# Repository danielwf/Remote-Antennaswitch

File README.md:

# ESP32 Antenna Switch 

for the Remote Club Station of [DARC Bremen (i04)](https://darc.de/i04)\
\
**This is a draft!** \
There is no guarantee of functionality. Use at your own risk. 

## Description

The antenna switch can be controlled via the ESP32 either by USB or WiFi. Two buttons can be connected for local control. The switched inputs and outputs are also indicated by LEDs.  
The 3 inputs and 5 outputs are switched using two bistable relays per connection (Finder 40.31.6.006.0000). These are controlled by drivers that can be put into sleep mode between switching operations (DRV8833PWP). This reduces power consumption and minimizes interference from busy switching regulators. In addition, the USB port of the ESP32 is sufficient for the power supply.  
The relay drivers are controlled via an I2C 16-bit port expander (MCP23017).  
In addition, a PWR/SWR meter is available via an I2C AD converter (ADS1115IDGS). This is used to prevent switching during transmission. It can also be used for transmitter-independent measurement to display transmission power and SWR in the remote software.  

Since both the relay switching and the reading of the SWR bridge are communicated via I2C, other controllers can also be used if necessary. It is also possible to connect several boards together. For this purpose, the I2C addresses can be easily adjusted via the solder pads.  

## Built

**Kicad 9:**
You maybe need the KiCad symbol and footprint for the ESP32 Mini(Wemos D1 Mini) [https://github.com/r0oland/ESP32_mini_KiCad_Library](https://github.com/r0oland/ESP32_mini_KiCad_Library) - Thanks to [Johannes Rebling](https://github.com/r0oland)

[Schematic](schematic.pdf)

**Hardware:**
Everything you need to prepare your PCB ordering with KiCAD is included. It is best to use a corresponding KiCAD plugin for this.  
In "BOM.ods" you will find the material list with links to the item numbers at Mouser and Reichelt. In the table, you can easily adjust how many devices the parts should be ordered for (as of Oct-25).  
The BOM includes a housing that is well suited for this purpose. The drill holes for the circuit board can be easily marked with an unassembled PCB (which should be done first). "Panels.svg" contains the drill holes and labels for the buttons, LEDs, and connection sockets. These can be produced using a vinyl cutter or laser engraver, for example. The easiest way to create the USB socket is to drill a 14 mm hole and produce a cover for it using a 3D printer. A template for this is also included.  
Once the parts have been assembled, the Arduino code for the ESP32 can be uploaded. You will find this in “AntennaSwitch-ESP32.ino”. For later OTA updates via the web interface, you can use “AntennaSwitch-ESP32.ino.bin”.  

## Usage WIFI
</img> After you have uploaded the Arduino code to the ESP32, you must connect to the “AntSwitch-Config” Wi-Fi network and set up the desired Wi-Fi network via the captive portal. 
Once the device is connected to your home network, you can configure it via 'https://antswitch.local' such as a new host name and the labels for the connectors. **Default password for 'admin' is 'antswitch'**.  
You can also switch via API (example: you want to use CURL in your shell/script, maybe in combination with rigctld). Examples: 
- http://antswitch.local/api/status (for JSON-Status)
- http://antswitch.local/api/switch?input=1 (set input to 1)
- http://antswitch.local/api/switch?output=2 (set output to 2)
Setup via API:
- http://antswitch.local/api/switch?iLabel1=IC-7300 (set Label of input 1)
- http://antswitch.local/api/switch?oLabel2=Windom-Antenna (set Label of output 2)
- http://antswitch.local/api/switch?defaultInput=1 (set default input after switch-on)
- http://antswitch.local/api/switch?defaultOutput=2 (set default output after switch-on)
- http://antswitch.local/api/status?maxTxPower=380 (Calibration of SWR-Meter acc to windings on transformer- or just try out and compare to other SWR-Meter)

## Usage USB-serial
The device can also be controlled via the USB-serial interface (115200 baud). With “GET:NET” you can display the current IP address.  
Serial commands: 
```
       ____DESCRIPTION__________INPUT_________________________RESPONSE___________________________________  
       Switching  
       Switch Input (TRX)          SET:I<Index>                  ACK:I<CurrentInput>,O<CurrentOutput>  
                                                                ERR:BLOCKED_TX (if P_fwd > 5.0W)  
       Switch Output (Antenna)     SET:O<Index>                  ACK:I<CurrentInput>,O<CurrentOutput>  
                                                                ERR:BLOCKED_TX (if P_fwd > 5.0W)  
       ___________________________________________________________________________________________________
       Configuration
       Set Input Label             SET_LABEL I <Index> <Label>   ACK:LABEL_OK
                                                                ERR:INVALID_LENGTH
       Set Output Label            SET_LABEL O <Index> <Label>   ACK:LABEL_OK
                                                                ERR:INVALID_LENGTH
       Set Default Input           SET_DEFAULT I <Index>         ACK:DEFAULT_OK
                                                                ERR:INVALID_INDEX
       Set Default Output          SET_DEFAULT O <Index>         ACK:DEFAULT_OK
                                                                ERR:INVALID_INDEX
       Set Admin Password          SET_PASS <Password>           ACK:PASS_OK
                                                                ERR:INVALID_LENGTH (min 8 chars)
       ___________________________________________________________________________________________________
       Status and Measurements
       Get All Status & Meas.      GET:STATUS                    ACK:STATUS,PF=x.x,PP=x.x,SWR=x.xx
       Get Forward Power (Formatted) GET:PF                        ACK:PF=x.x
       Get Peak Power (Formatted)  GET:PP                        ACK:PP=x.x
       Get SWR Value (Formatted)   GET:SWR                       ACK:SWR=x.xx
       Get Forward Power (Numeric) NUM:PF                        [x.x] (Unformatted numeric value)
       Get Peak Power (Numeric)    NUM:PP                        [x.x] (Unformatted numeric value)
       Get SWR Value (Numeric)     NUM:SWR                       [x.xx] (Unformatted numeric value)
       Get IP and Hostname         GET:NET                       ACK:NET,IP=x.x.x.x,HOST=<Hostname>
       Get Input Label             GET_LABEL I <Index>           ACK:LABEL_I<Index>=<Label>
       Get Output Label            GET_LABEL O <Index>           ACK:LABEL_O<Index>=<Label>
```

## Contributing

Pull requests are welcome. For major changes, please open an issue first
to discuss what you would like to change.

## License

[CC BY-SA 4.0](https://creativecommons.org/licenses/by-sa/4.0/)

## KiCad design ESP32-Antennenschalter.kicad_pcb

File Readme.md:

# ESP32 Antenna Switch 

for the Remote Club Station of [DARC Bremen (i04)](https://darc.de/i04)\
\
**This is a draft!** \
There is no guarantee of functionality. Use at your own risk. 

**ToDos**
 - BOM
 - 3D design for FDM printers and shielding
 - Arduino Code
 - first builds

## Description

The antenna switch can be controlled via the ESP32 either by USB, WiFi, or Bluetooth, depending on what is implemented in the code. Two buttons can be connected for local control. The switched inputs and outputs are also indicated by LEDs. 

The 3 inputs and 5 outputs are switched using two bistable relays per connection (Finder 40.31.6.006.0000). These are controlled by drivers that can be put into sleep mode between switching operations (DRV8833PWP). This reduces power consumption and minimizes interference from busy switching regulators. In addition, the USB port of the ESP32 is sufficient for the power supply. 

The relay drivers are controlled via an I2C 16-bit port expander (MCP23017). 
In addition, a PWR/SWR meter is available via an I2C AD converter (ADS1115IDGS). This is used to prevent switching during transmission. It can also be used for transmitter-independent measurement to display transmission power and SWR in the remote software. 

Since both the relay switching and the reading of the SWR bridge are communicated via I2C, other controllers can also be used if necessary. It is also possible to connect several boards together. For this purpose, the I2C addresses can be easily adjusted via the solder pads. 

## Usage

**Kicad 9:**
You maybe need the KiCad symbol and footprint for the ESP32 Mini(Wemos D1 Mini) [https://github.com/r0oland/ESP32_mini_KiCad_Library](https://github.com/r0oland/ESP32_mini_KiCad_Library) - Thanks to [Johannes Rebling](https://github.com/r0oland)

## Contributing

Pull requests are welcome. For major changes, please open an issue first
to discuss what you would like to change.

## License

[CC BY-SA 4.0](https://creativecommons.org/licenses/by-sa/4.0/)

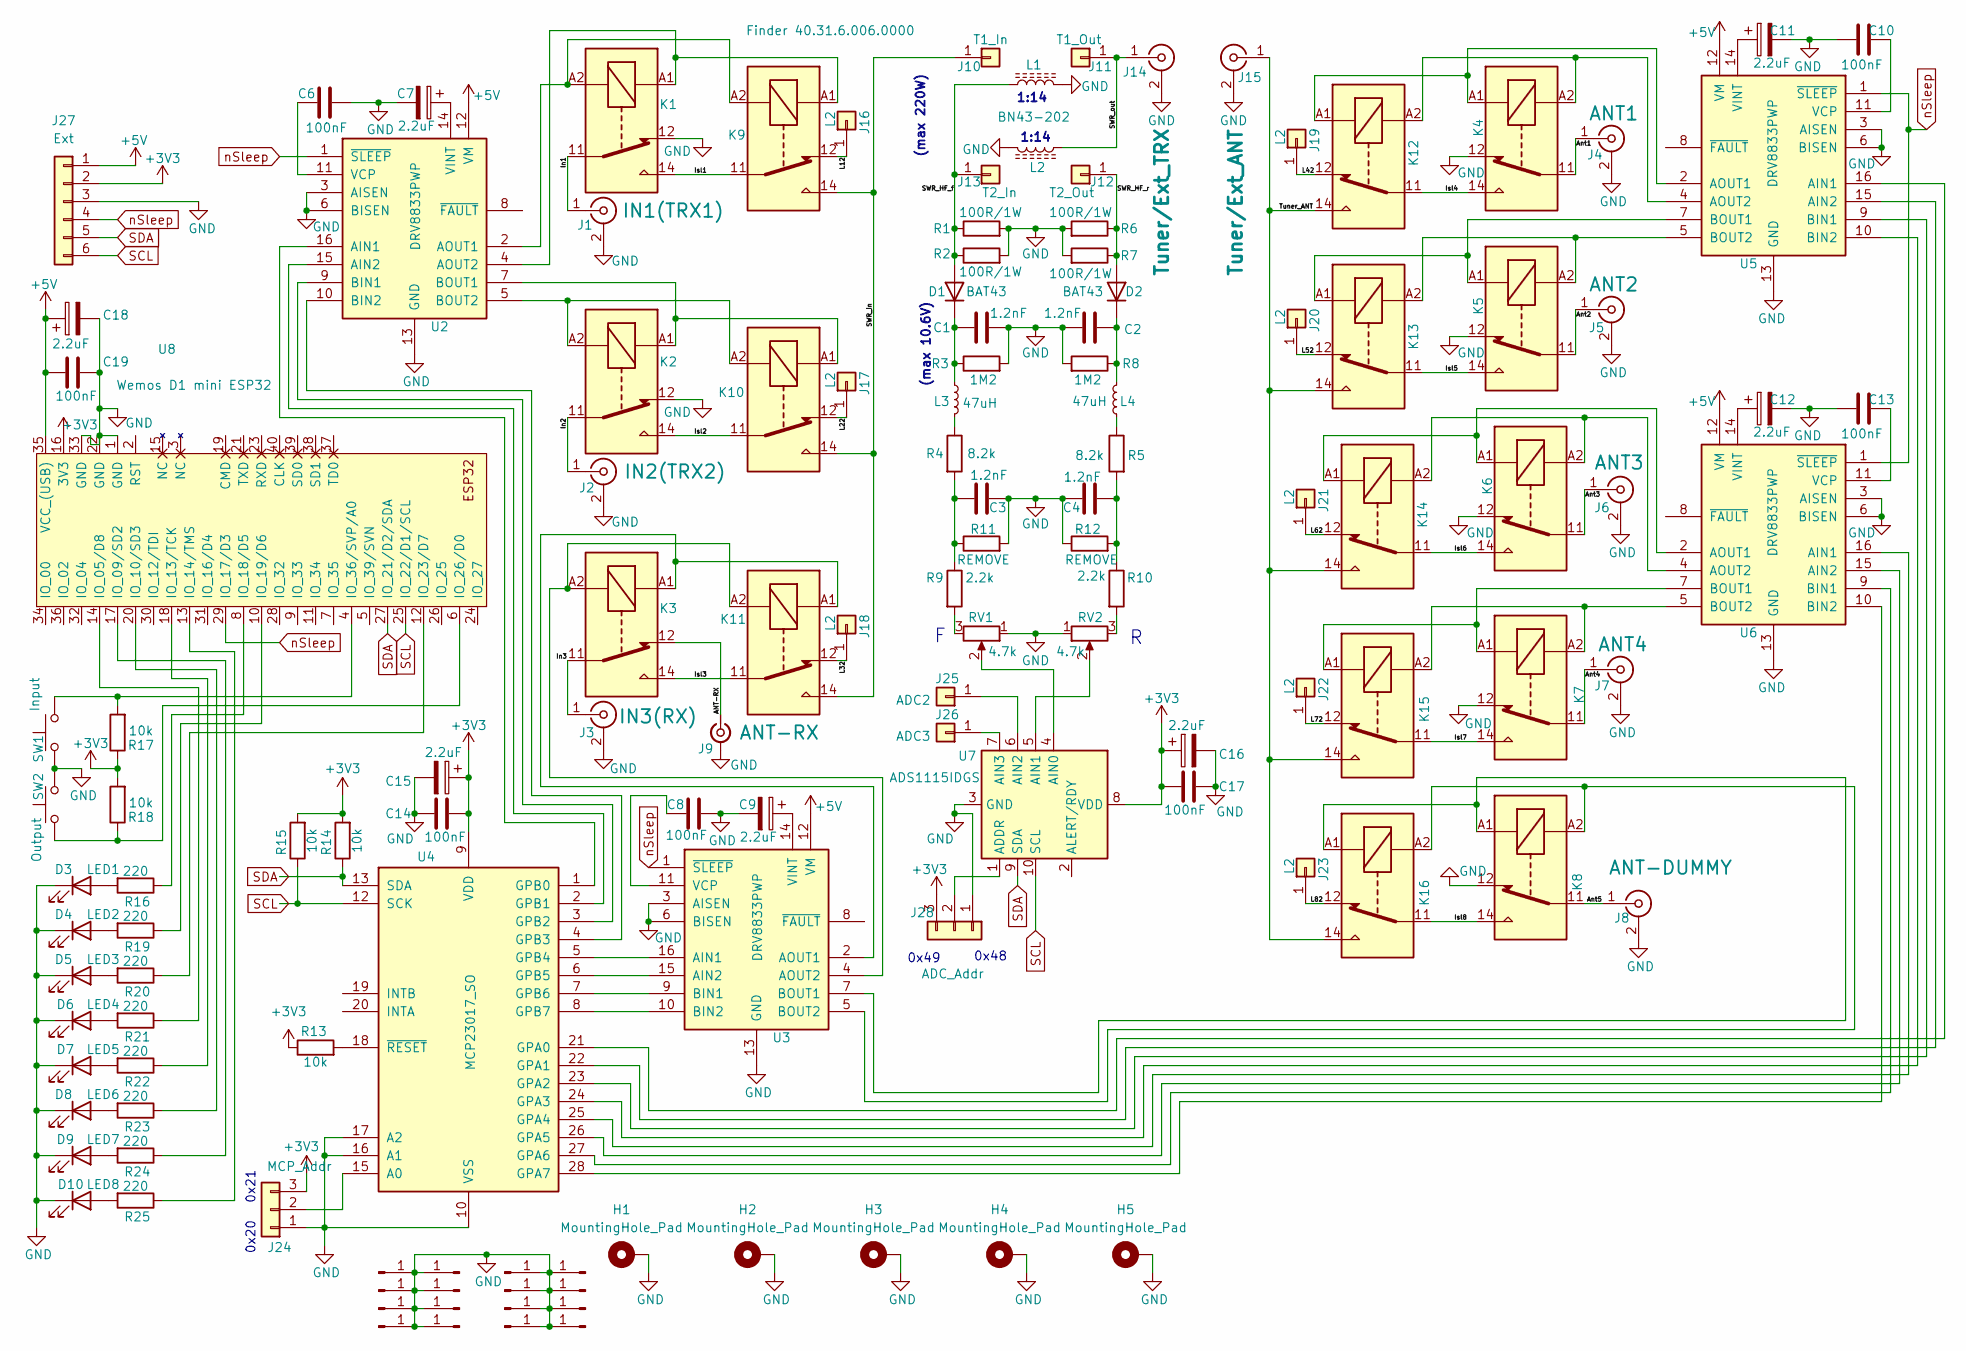
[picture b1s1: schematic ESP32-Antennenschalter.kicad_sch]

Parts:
C1, C2, C3, C4: 1.2nF; C_Disc_D4.3mm_W1.9mm_P5.00mm
C6, C8, C10, C13, C14, C17, C19: 100nF; C_Disc_D4.3mm_W1.9mm_P5.00mm
C7, C9, C11, C12, C15, C16, C18: 2.2uF; CP_Radial_D5.0mm_P2.00mm
D1, D2: BAT43; D_DO-35_SOD27_P7.62mm_Horizontal
D3: LED1; LED_D3.0mm
D4: LED2; LED_D3.0mm
D5: LED3; LED_D3.0mm
D6: LED4; LED_D3.0mm
D7: LED5; LED_D3.0mm
D8: LED6; LED_D3.0mm
D9: LED7; LED_D3.0mm
D10: LED8; LED_D3.0mm
H1, H2, H3, H4, H5: MountingHole_Pad; MountingHole_3.2mm_M3_DIN965_Pad_TopBottom
J1: IN1(TRX1); TerminalBlock_bornier-2_P5.08mm
J2: IN2(TRX2); TerminalBlock_bornier-2_P5.08mm
J3: IN3(RX); TerminalBlock_bornier-2_P5.08mm
J4: ANT1; TerminalBlock_bornier-2_P5.08mm
J5: ANT2; TerminalBlock_bornier-2_P5.08mm
J6: ANT3; TerminalBlock_bornier-2_P5.08mm
J7: ANT4; TerminalBlock_bornier-2_P5.08mm
J8: ANT-DUMMY; TerminalBlock_bornier-2_P5.08mm
J9: ANT-RX; PinHeader_1x02_P2.54mm_Vertical
J10: T1_In; Pin_D1.3mm_L11.0mm_LooseFit
J11: T1_Out; Pin_D1.3mm_L11.0mm_LooseFit
J12: T2_Out; Pin_D1.3mm_L11.0mm_LooseFit
J13: T2_In; Pin_D1.3mm_L11.0mm_LooseFit
J14: Tuner/Ext_TRX; TerminalBlock_bornier-2_P5.08mm
J15: Tuner/Ext_ANT; TerminalBlock_bornier-2_P5.08mm
J16, J17, J18, J19, J20, J21, J22, J23: L2; Pin_D0.7mm_L6.5mm_W1.8mm_FlatFork
J24: MCP_Addr; SolderJumper-3_P1.3mm_Bridged2Bar12_Pad1.0x1.5mm_NumberLabe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
J25: ADC2; Pin_D0.7mm_L6.5mm_W1.8mm_FlatFork
J26: ADC3; Pin_D0.7mm_L6.5mm_W1.8mm_FlatFork
J27: Ext; PinHeader_1x06_P2.54mm_Vertical
J28: ADC_Addr; SolderJumper-3_P1.3mm_Bridged2Bar12_Pad1.0x1.5mm_NumberLabe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
J29, J30, J31, J32, J33, J34, J35, J36, J37, J38, J39, J40, J41, J42, J43, J44: Conn_01x01_Pin; Pin_D0.7mm_L6.5mm_W1.8mm_FlatFork
K1, K2, K3, K4, K5, K6, K7, K8, K9, K10, K11, K12, K13, K14, K15, K16: Finder 40.31.6.006.0000; Relay_SPDT_Finder_40.31
L1, L2: BN43-202; L_Axial_L14.5mm_D5.8mm_P25.40mm_Horizontal_Fastron_HBCC
L3, L4: 47uH; L_Axial_L7.0mm_D3.3mm_P10.16mm_Horizontal_Fastron_MICC
R1, R2, R6, R7: 100R/1W; R_Axial_DIN0207_L6.3mm_D2.5mm_P5.08mm_Vertical
R3, R8: 1M2; R_Axial_DIN0207_L6.3mm_D2.5mm_P5.08mm_Vertical
R4, R5: 8.2k; R_Axial_DIN0207_L6.3mm_D2.5mm_P5.08mm_Vertical
R9, R10: 2.2k; R_Axial_DIN0207_L6.3mm_D2.5mm_P5.08mm_Vertical
R11, R12: REMOVE; R_Axial_DIN0207_L6.3mm_D2.5mm_P5.08mm_Vertical
R13, R14, R15, R17, R18: 10k; R_Axial_DIN0204_L3.6mm_D1.6mm_P7.62mm_Horizontal
R16, R19, R20, R21, R22, R23, R24, R25: 220; R_Axial_DIN0204_L3.6mm_D1.6mm_P7.62mm_Horizontal
RV1, RV2: 4.7k; Potentiometer_Vishay_T93YA_Vertical
SW1: Input; PinHeader_1x02_P2.54mm_Vertical
SW2: Output; PinHeader_1x02_P2.54mm_Vertical
U2, U3, U5, U6: DRV8833PWP; HTSSOP-16-1EP_4.4x5mm_P0.65mm_EP3.4x5mm_Mask2.46x2.31mm_The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
U4: MCP23017_SO; SOIC-28W_7.5x17.9mm_P1.27mm
U7: ADS1115IDGS; TSSOP-10_3x3mm_P0.5mm
U8: Wemos D1 mini ESP32; ESP32_mini

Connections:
+3V3: C14.1, C15.1, C16.1, C17.1, J24.3, J27.2, J28.3, R13.1, R14.2, R15.2, R17.1, R18.2, U4.9 (VDD), U7.8 (VDD), U8.16 (3V3)
+5V: C18.1, C19.2, J27.1, U2.12 (VM), U3.12 (VM), U5.12 (VM), U6.12 (VM), U8.35 (VCC_(USB))
/ANT-RX: J9.1 (In), K3.12
/Ant1: J4.1 (In), K4.11
/Ant2: J5.1 (In), K5.11
/Ant3: J6.1 (In), K6.11
/Ant4: J7.1 (In), K7.11
/Ant5: J8.1 (In), K8.11
/In1: J1.1 (In), K1.11
/In2: J2.1 (In), K2.11
/In3: J3.1 (In), K3.11
/Isl1: K1.14, K9.11
/Isl2: K2.14, K10.11
/Isl3: K3.14, K11.11
/Isl4: K4.14, K12.11
/Isl5: K5.14, K13.11
/Isl6: K6.14, K14.11
/Isl7: K7.14, K15.11
/Isl8: K8.14, K16.11
/L12: J16.1, K9.12
/L22: J17.1, K10.12
/L32: J18.1, K11.12
/L42: J19.1, K12.12
/L52: J20.1, K13.12
/L62: J21.1, K14.12
/L72: J22.1, K15.12
/L82: J23.1, K16.12
/SWR_HF_f: D1.2 (A), J13.1, L1.1, R1.1, R2.1
/SWR_HF_r: D2.2 (A), J12.1, R6.1, R7.1
/SWR_in: J10.1, K9.14, K10.14, K11.14
/SWR_out: J11.1, J14.1 (In), L2.1
/Tuner_ANT: J15.1 (In), K12.14, K13.14, K14.14, K15.14, K16.14
GND: C1.2, C2.2, C3.2, C4.1, C6.1, C7.2, C8.1, C9.2, C10.1, C11.2, C12.2, C13.1, C14.2, C15.2, C16.2, C17.2, C18.2, C19.1, D3.1 (K), D4.1 (K), D5.1 (K), D6.1 (K), D7.1 (K), D8.1 (K), D9.1 (K), D10.1 (K), H1.1, H2.1, H3.1, H4.1, H5.1, J1.2 (Ext), J2.2 (Ext), J3.2 (Ext), J4.2 (Ext), J5.2 (Ext), J6.2 (Ext), J7.2 (Ext), J8.2 (Ext), J9.2 (Ext), J14.2 (Ext), J15.2 (Ext), J24.1, J27.3, J28.1, J29.1, J30.1, J31.1, J32.1, J33.1, J34.1, J35.1, J36.1, J37.1, J38.1, J39.1, J40.1, J41.1, J42.1, J43.1, J44.1, K1.12, K2.12, K4.12, K5.12, K6.12, K7.12, K8.12, L1.2, L2.2, R1.2, R2.2, R3.2, R6.2, R7.2, R8.2, R11.2, R12.1, RV1.1, RV2.1, SW1.1, SW2.2, U2.3 (AISEN), U2.6 (BISEN), U2.13 (GND), U2.17 (GND), U3.3 (AISEN), U3.6 (BISEN), U3.13 (GND), U3.17 (GND), U4.10 (VSS), U4.16 (A1), U4.17 (A2), U5.3 (AISEN), U5.6 (BISEN), U5.13 (GND), U5.17 (GND), U6.3 (AISEN), U6.6 (BISEN), U6.13 (GND), U6.17 (GND), U7.3 (GND), U8.1 (GND), U8.22 (GND), U8.33 (GND)
unnamed: C3.1, R4.2, R9.1, R11.1
unnamed: C4.2, R5.2, R10.1, R12.2
unnamed: C1.1, D1.1 (K), L3.1, R3.1
unnamed: C2.1, D2.1 (K), L4.1, R8.1
unnamed: D3.2 (A), R16.2
unnamed: D4.2 (A), R19.2
unnamed: D5.2 (A), R20.2
unnamed: D6.2 (A), R21.2
unnamed: D7.2 (A), R22.2
unnamed: D8.2 (A), R23.2
unnamed: D9.2 (A), R24.2
unnamed: D10.2 (A), R25.2
unnamed: J24.2, U4.15 (A0)
unnamed: J25.1, U7.6 (AIN2)
unnamed: J26.1, U7.7 (AIN3)
unnamed: J28.2, U7.1 (ADDR)
unnamed: L3.2, R4.1
unnamed: L4.2, R5.1
unnamed: R9.2, RV1.3
unnamed: R10.2, RV2.3
unnamed: U2.16 (AIN1), U4.1 (GPB0)
unnamed: U2.15 (AIN2), U4.2 (GPB1)
unnamed: K1.A2, K9.A2, U2.2 (AOUT1)
unnamed: K1.A1, K9.A1, U2.4 (AOUT2)
unnamed: U2.9 (BIN1), U4.3 (GPB2)
unnamed: U2.10 (BIN2), U4.4 (GPB3)
unnamed: K2.A1, K10.A1, U2.7 (BOUT1)
unnamed: K2.A2, K10.A2, U2.5 (BOUT2)
unnamed: C6.2, U2.11 (VCP)
unnamed: C7.1, U2.14 (VINT)
unnamed: U3.16 (AIN1), U4.5 (GPB4)
unnamed: U3.15 (AIN2), U4.6 (GPB5)
unnamed: K3.A1, K11.A1, U3.2 (AOUT1)
unnamed: K3.A2, K11.A2, U3.4 (AOUT2)
unnamed: U3.9 (BIN1), U4.7 (GPB6)
unnamed: U3.10 (BIN2), U4.8 (GPB7)
unnamed: K8.A1, K16.A1, U3.7 (BOUT1)
unnamed: K8.A2, K16.A2, U3.5 (BOUT2)
unnamed: C8.2, U3.11 (VCP)
unnamed: C9.1, U3.14 (VINT)
unnamed: U4.21 (GPA0), U5.16 (AIN1)
unnamed: U4.22 (GPA1), U5.15 (AIN2)
unnamed: U4.23 (GPA2), U5.9 (BIN1)
unnamed: U4.24 (GPA3), U5.10 (BIN2)
unnamed: U4.25 (GPA4), U6.16 (AIN1)
unnamed: U4.26 (GPA5), U6.15 (AIN2)
unnamed: U4.27 (GPA6), U6.9 (BIN1)
unnamed: U4.28 (GPA7), U6.10 (BIN2)
unnamed: R13.2, U4.18 (~RESET)
unnamed: K4.A1, K12.A1, U5.2 (AOUT1)
unnamed: K4.A2, K12.A2, U5.4 (AOUT2)
unnamed: K5.A1, K13.A1, U5.7 (BOUT1)
unnamed: K5.A2, K13.A2, U5.5 (BOUT2)
unnamed: C10.2, U5.11 (VCP)
unnamed: C11.1, U5.14 (VINT)
unnamed: K6.A1, K14.A1, U6.2 (AOUT1)
unnamed: K6.A2, K14.A2, U6.4 (AOUT2)
unnamed: K7.A1, K15.A1, U6.7 (BOUT1)
unnamed: K7.A2, K15.A2, U6.5 (BOUT2)
unnamed: C13.2, U6.11 (VCP)
unnamed: C12.1, U6.14 (VINT)
unnamed: RV1.2, U7.4 (AIN0)
unnamed: RV2.2, U7.5 (AIN1)
unnamed: R21.1, U8.14 (IO_05/D8)
unnamed: R24.1, U8.17 (IO_09/SD2)
unnamed: R23.1, U8.20 (IO_10/SD3)
unnamed: R22.1, U8.18 (IO_13/TCK)
unnamed: R25.1, U8.13 (IO_14/TMS)
unnamed: R16.1, U8.8 (IO_18/D5)
unnamed: R19.1, U8.10 (IO_19/D6)
unnamed: R20.1, U8.12 (IO_23/D7)
unnamed: R18.1, SW2.1, U8.6 (IO_26/D0)
unnamed: R17.2, SW1.2, U8.4 (IO_36/SVP/A0)
SCL: J27.6, R15.1, U4.12 (SCK), U7.10 (SCL), U8.25 (IO_22/D1/SCL)
SDA: J27.5, R14.1, U4.13 (SDA), U7.9 (SDA), U8.27 (IO_21/D2/SDA)
nSleep: J27.4, U2.1 (~SLEEP), U3.1 (~SLEEP), U5.1 (~SLEEP), U6.1 (~SLEEP), U8.29 (IO_17/D3)

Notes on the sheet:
(max 10.6V)
0x20
0x49
0x48
(max 220W)
1:14
0x21

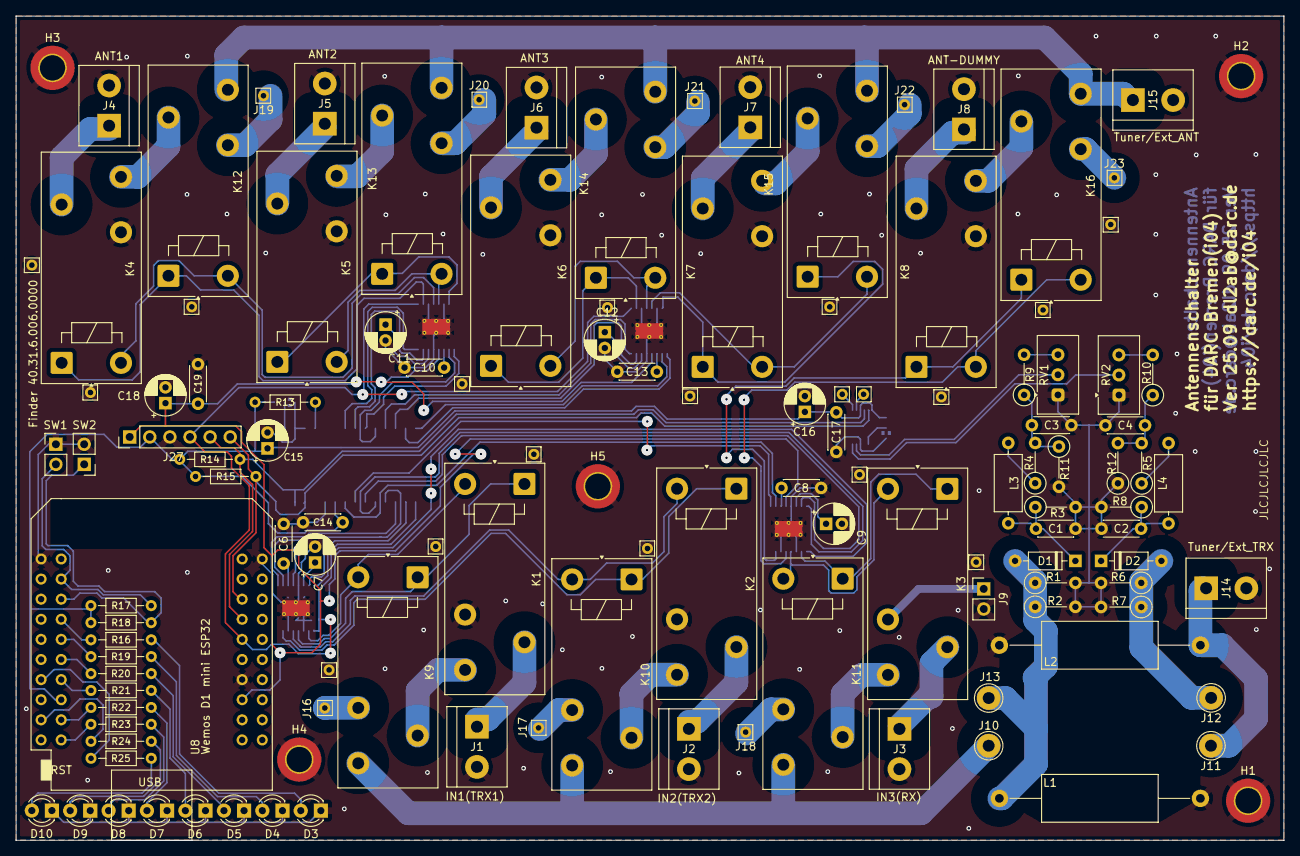
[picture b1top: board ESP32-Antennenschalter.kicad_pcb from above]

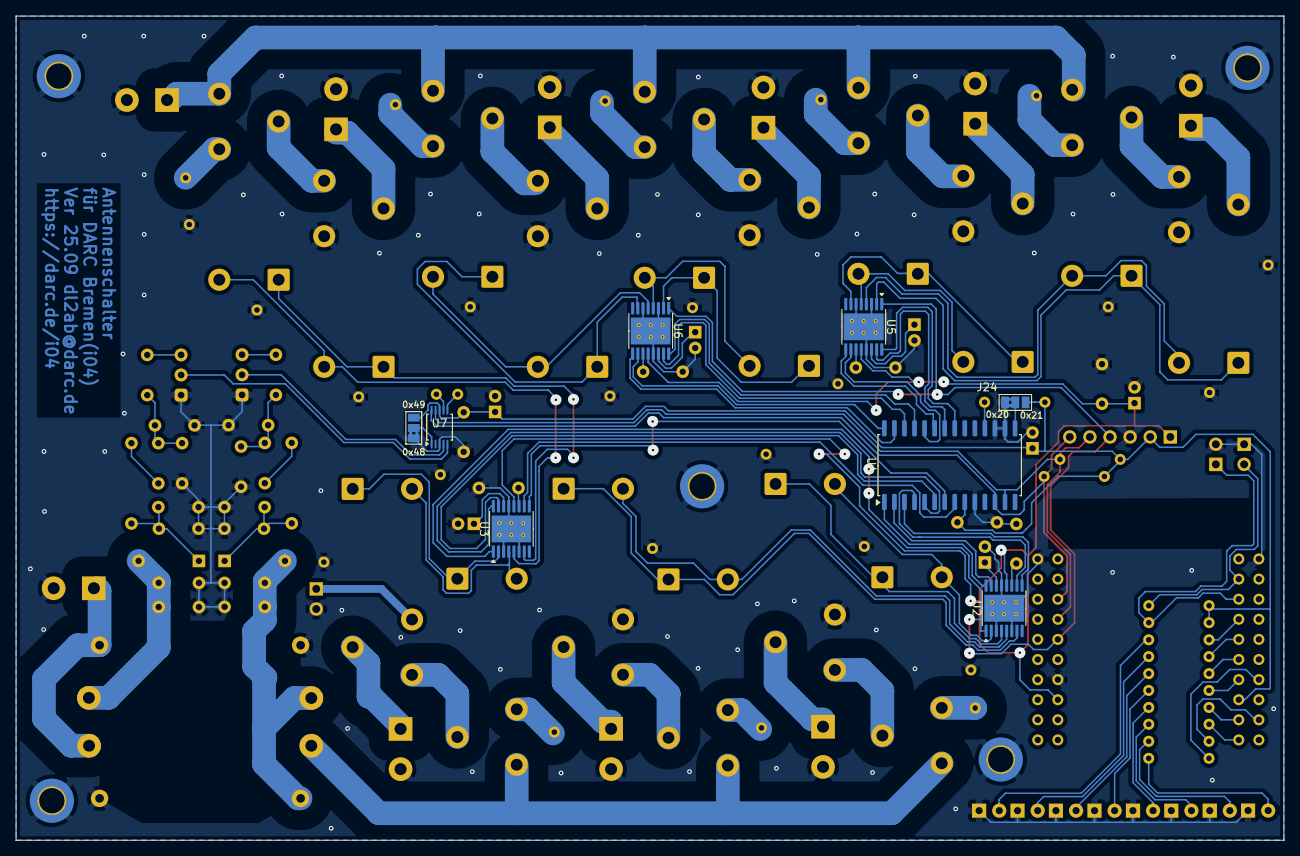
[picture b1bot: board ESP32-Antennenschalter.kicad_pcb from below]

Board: 2 copper layers, 160.2 x 104.1 mm, 133 parts (8 on the bottom side), 109 nets.

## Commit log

2025-09-06 added vias for better shielding
2025-09-07 BOM (mouser, reichelt, prices for 3 units)
2025-10-23 Arduino-Code for Wemos D1 Mini ESP32
    See Code for Documentation
2025-10-26 repaired broken GND-connection of U2
2025-10-26 updated layout (repaired GND-connection at U2)
2025-10-26 Buttons and OTA-Update
2025-11-02 Added SVG template for labels and drill holes
    The drill holes for the PCB and case feet depend on the case. It is best to use the unassembled PCB to mark the corresponding holes.
    I would recommend drilling the holes for the LEDs first, inserting them, and soldering them to the PCB with wires.
2025-11-02 USB-C-Cover for 14mm drilling hole
2025-11-02 example web interface
2025-11-06 Better Layout for LEDs
2025-11-06 wider opening
2025-11-11 SWR-Meter: Remove R11,R23; Replace R4,R5 with 8.2K
2025-11-11 added PWR/SWR-Calibration + some minor changes
2025-12-14 reset every 3min if not connected to known wifi
    After power failures, the antenna switch starts up faster than the WiFi router, causing the antenna switch to switch to WiFi configuration mode and remain there. To prevent this, the antenna switch n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
2025-12-14 reset Antswitch after 3min in wifi-config
    After power failures, the antenna switch starts up faster than the WiFi router, causing the antenna switch to switch to WiFi configuration mode and remain there. To prevent this, the antenna switch n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
2025-12-14 reset after 3min in wifi-config-mode
    After power failures, the antenna switch starts up faster than the WiFi router, causing the antenna switch to switch to WiFi configuration mode and remain there. To prevent this, the antenna switch n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
2025-12-28 Update README.md
    detailed API-description
2026-04-19 Add files via upload
    Power(peak) reset was not working. Reset-Level set to 0.1W
2026-05-03 Add files via upload
    added editing of local label file (.ports) in Browserinterface
